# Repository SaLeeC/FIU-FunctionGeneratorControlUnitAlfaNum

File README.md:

# FIU-FunctionGeneratorControlUnitAlfaNum
FIU - Function Generator Control Unit Alphanumeric

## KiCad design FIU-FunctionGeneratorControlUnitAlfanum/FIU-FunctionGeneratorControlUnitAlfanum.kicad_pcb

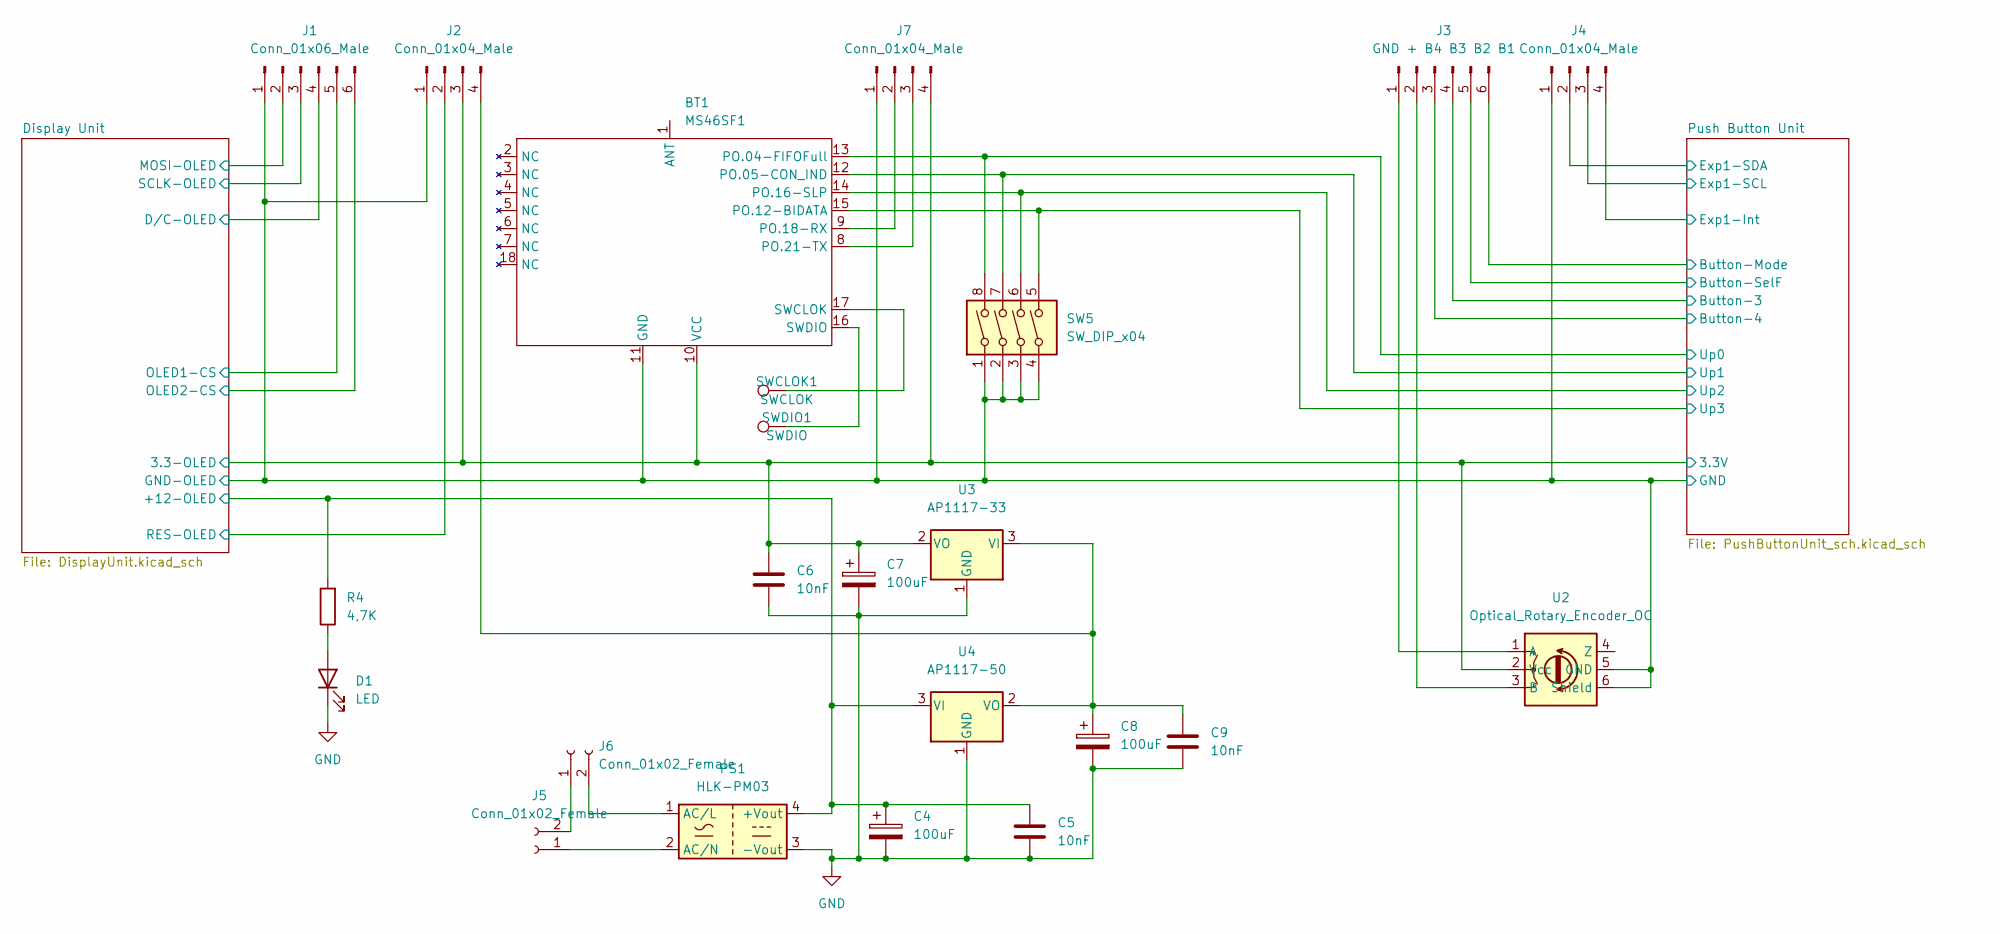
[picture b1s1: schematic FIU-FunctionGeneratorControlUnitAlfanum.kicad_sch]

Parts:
BT1: MS46SF1; MS46SF11
C4, C7, C8: 100uF; CP_Radial_D8.0mm_P5.00mm
C5, C6, C9: 10nF; C_1206_3216Metric
D1: LED; LED_D3.0mm
J1: Conn_01x06_Male; PinHeader_1x06_P2.54mm_Vertical
J2, J4, J7: Conn_01x04_Male; PinHeader_1x04_P2.54mm_Vertical
J3: GND + B4 B3 B2 B1; PinHeader_1x06_P2.54mm_Vertical
J5, J6: Conn_01x02_Female; PinSocket_1x02_P2.54mm_Vertical
PS1: HLK-PM03; CONV_HLK-5M05
R4: 4,7K; R_1206_3216Metric
SW5: SW_DIP_x04; DIP-8_W10.16mm_LongPads
SWCLOK1: SWCLOK; TestPoint_Pad_D1.5mm
SWDIO1: SWDIO; TestPoint_Pad_D1.5mm
U2: Optical_Rotary_Encoder_OC; Rotary Encoder Optical
U3: AP1117-33; SOT-223-3_TabPin2
U4: AP1117-50; SOT-223-3_TabPin2

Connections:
+3V3: BT1.10 (VCC), C6.1, C7.1, J2.3, J7.4, U2.2 (Vcc), U3.2 (VO); also elsewhere on the board
+12V: C4.1, C5.1, PS1.4 (+Vout), R4.2, U4.3 (VI); also elsewhere on the board
/Display Unit/D/C-OLED: J1.4; also elsewhere on the board
/Display Unit/MOSI-OLED: J1.2; also elsewhere on the board
/Display Unit/OLED1-CS: J1.5; also elsewhere on the board
/Display Unit/OLED2-CS: J1.6; also elsewhere on the board
/Display Unit/RES-OLED: J2.2; also elsewhere on the board
/Display Unit/SCLK-OLED: J1.3; also elsewhere on the board
/Push Button Unit/Button-3: J3.4; also elsewhere on the board
/Push Button Unit/Button-4: J3.3; also elsewhere on the board
/Push Button Unit/Button-Mode: J3.6; also elsewhere on the board
/Push Button Unit/Button-SelF: J3.5; also elsewhere on the board
/Push Button Unit/Exp1-Int: J4.4; also elsewhere on the board
/Push Button Unit/Exp1-SCL: J4.3; also elsewhere on the board
/Push Button Unit/Exp1-SDA: J4.2; also elsewhere on the board
/Push Button Unit/Up0: BT1.13 (PO.04-FIFOFull), SW5.8; also elsewhere on the board
/Push Button Unit/Up1: BT1.12 (PO.05-CON_IND), SW5.7; also elsewhere on the board
/Push Button Unit/Up2: BT1.14 (PO.16-SLP), SW5.6; also elsewhere on the board
/Push Button Unit/Up3: BT1.15 (PO.12-BIDATA), SW5.5; also elsewhere on the board
GND: BT1.11 (GND), C4.2, C5.2, C6.2, C7.2, C8.2, C9.2, D1.1 (K), J1.1, J2.1, J4.1, J7.1, PS1.3 (-Vout), SW5.1, SW5.2, SW5.3, SW5.4, U2.5 (GND), U2.6 (Shield), U3.1 (GND), U4.1 (GND); also elsewhere on the board
unnamed: BT1.8 (PO.21-TX), J7.3
unnamed: BT1.9 (PO.18-RX), J7.2
unnamed: BT1.16 (SWDIO), SWDIO1.1
unnamed: BT1.17 (SWCLOK), SWCLOK1.1
unnamed: D1.2 (A), R4.1
unnamed: C8.1, C9.1, J2.4, U3.3 (VI), U4.2 (VO)
unnamed: J3.1, U2.1 (A)
unnamed: J3.2, U2.3 (B)
unnamed 30: J5.1, PS1.2 (AC/N); also elsewhere on the board
unnamed 31: J5.2, J6.1; also elsewhere on the board
unnamed 32: J6.2, PS1.1 (AC/L); also elsewhere on the board

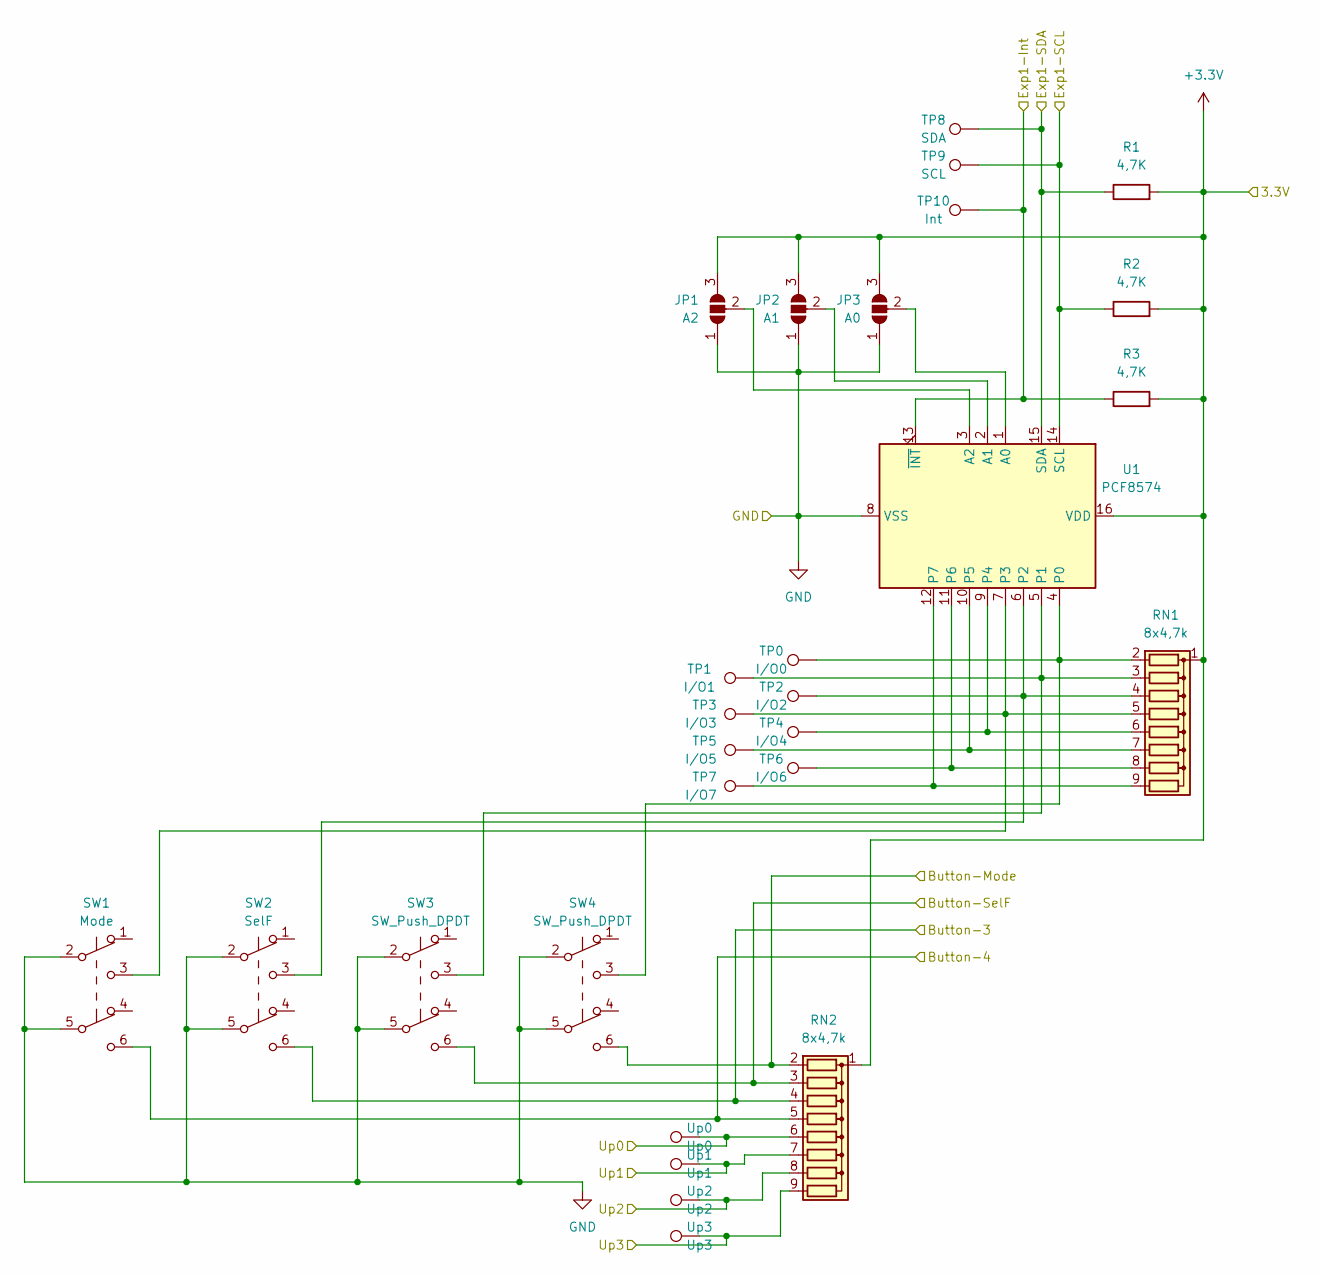
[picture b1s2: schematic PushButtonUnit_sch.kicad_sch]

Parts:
JP1: A2; SolderJumper-3_P1.3mm_Open_RoundedPad1.0x1.5mm
JP2: A1; SolderJumper-3_P1.3mm_Open_RoundedPad1.0x1.5mm
JP3: A0; SolderJumper-3_P1.3mm_Open_RoundedPad1.0x1.5mm
R1, R2, R3: 4,7K; R_1206_3216Metric
RN1, RN2: 8x4,7k; R_Array_SIP9
SW1: Mode; PushDevDouble
SW2: SelF; PushDevDouble
SW3, SW4: SW_Push_DPDT; PushDevDouble
TP0: I/O0; TestPoint_Pad_D1.5mm
TP1: I/O1; TestPoint_Pad_D1.5mm
TP2: I/O2; TestPoint_Pad_D1.5mm
TP3: I/O3; TestPoint_Pad_D1.5mm
TP4: I/O4; TestPoint_Pad_D1.5mm
TP5: I/O5; TestPoint_Pad_D1.5mm
TP6: I/O6; TestPoint_Pad_D1.5mm
TP7: I/O7; TestPoint_Pad_D1.5mm
TP8: SDA; TestPoint_Pad_D1.5mm
TP9: SCL; TestPoint_Pad_D1.5mm
TP10: Int; TestPoint_Pad_D1.5mm
U1: PCF8574; SOIC-16_4.55x10.3mm_P1.27mm
Up0: Up0; TestPoint_Pad_D1.5mm
Up1: Up1; TestPoint_Pad_D1.5mm
Up2: Up2; TestPoint_Pad_D1.5mm
Up3: Up3; TestPoint_Pad_D1.5mm

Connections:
+3V3: JP1.3 (B), JP2.3 (B), JP3.3 (B), R1.2, R2.2, R3.2, RN1.1 (common), RN2.1 (common), U1.16 (VDD); also elsewhere on the board
/Push Button Unit/Button-3: RN2.4 (R3), SW2.6 (C); also elsewhere on the board
/Push Button Unit/Button-4: RN2.5 (R4), SW1.6 (C); also elsewhere on the board
/Push Button Unit/Button-Mode: RN2.2 (R1), SW4.6 (C); also elsewhere on the board
/Push Button Unit/Button-SelF: RN2.3 (R2), SW3.6 (C); also elsewhere on the board
/Push Button Unit/Exp1-Int: R3.1, TP10.1, U1.13 (~INT); also elsewhere on the board
/Push Button Unit/Exp1-SCL: R2.1, TP9.1, U1.14 (SCL); also elsewhere on the board
/Push Button Unit/Exp1-SDA: R1.1, TP8.1, U1.15 (SDA); also elsewhere on the board
/Push Button Unit/Up0: RN2.6 (R5), Up0.1; also elsewhere on the board
/Push Button Unit/Up1: RN2.7 (R6), Up1.1; also elsewhere on the board
/Push Button Unit/Up2: RN2.8 (R7), Up2.1; also elsewhere on the board
/Push Button Unit/Up3: RN2.9 (R8), Up3.1; also elsewhere on the board
GND: JP1.1 (A), JP2.1 (A), JP3.1 (A), SW1.2 (B), SW1.5 (B), SW2.2 (B), SW2.5 (B), SW3.2 (B), SW3.5 (B), SW4.2 (B), SW4.5 (B), U1.8 (VSS); also elsewhere on the board
unnamed: JP1.2 (C), U1.3 (A2)
unnamed: JP2.2 (C), U1.2 (A1)
unnamed: JP3.2 (C), U1.1 (A0)
unnamed: RN1.2 (R1), SW4.3 (C), TP0.1, U1.4 (P0)
unnamed: RN1.3 (R2), SW3.3 (C), TP1.1, U1.5 (P1)
unnamed: RN1.4 (R3), SW2.3 (C), TP2.1, U1.6 (P2)
unnamed: RN1.5 (R4), SW1.3 (C), TP3.1, U1.7 (P3)
unnamed: RN1.6 (R5), TP4.1, U1.9 (P4)
unnamed: RN1.7 (R6), TP5.1, U1.10 (P5)
unnamed: RN1.8 (R7), TP6.1, U1.11 (P6)
unnamed: RN1.9 (R8), TP7.1, U1.12 (P7)

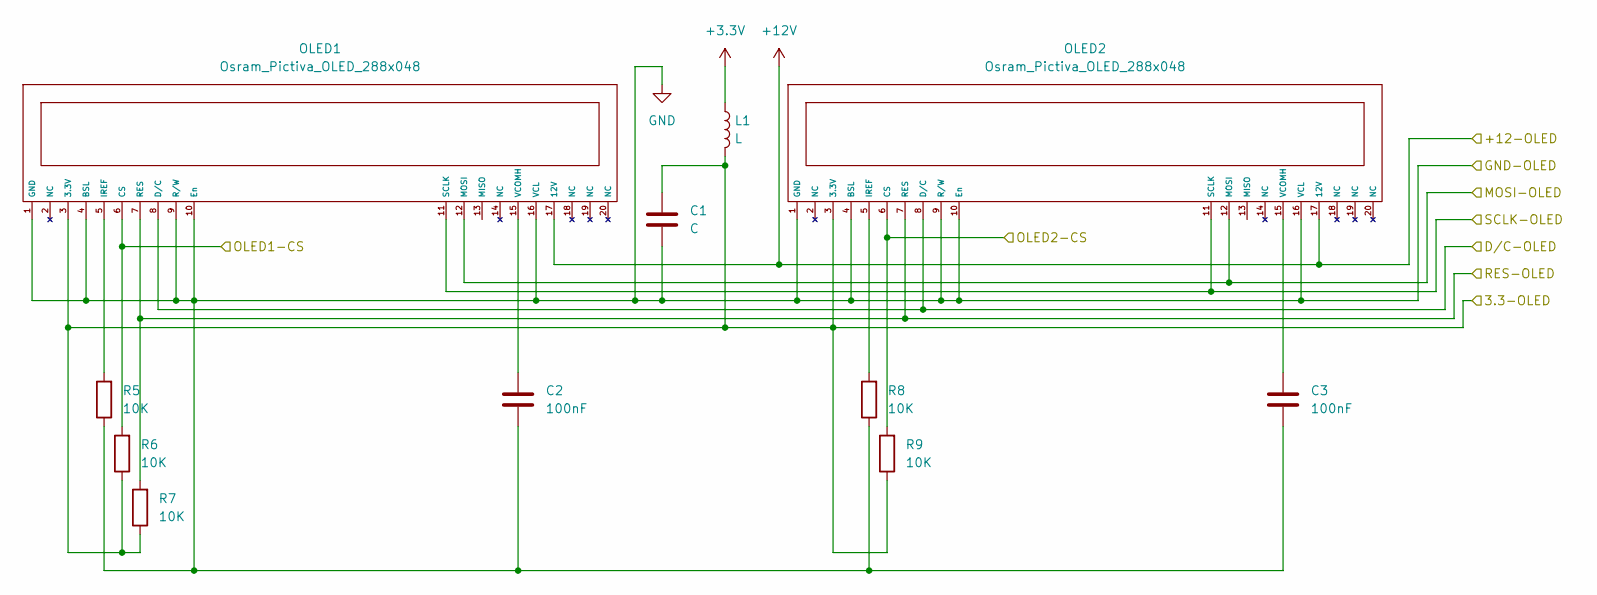
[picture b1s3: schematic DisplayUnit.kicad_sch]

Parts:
C1: C; C_1206_3216Metric
C2, C3: 100nF; C_1206_3216Metric
L1: L; L_1206_3216Metric
OLED1, OLED2: Osram_Pictiva_OLED_288x048; Osram Pictiva 288x048
R5, R6, R7, R8, R9: 10K; R_1206_3216Metric

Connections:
+3V3: C1.1, L1.1, L1.2, OLED1.3 (3.3V), OLED2.3 (3.3V), R6.1, R7.1, R9.1; also elsewhere on the board
+12V: OLED1.17 (12V), OLED2.17 (12V); also elsewhere on the board
/Display Unit/D/C-OLED: OLED1.8 (D/C), OLED2.8 (D/C); also elsewhere on the board
/Display Unit/MOSI-OLED: OLED1.12 (MOSI), OLED2.12 (MOSI); also elsewhere on the board
/Display Unit/OLED1-CS: OLED1.6 (CS), R6.2; also elsewhere on the board
/Display Unit/OLED2-CS: OLED2.6 (CS), R9.2; also elsewhere on the board
/Display Unit/RES-OLED: OLED1.7 (RES), OLED2.7 (RES), R7.2; also elsewhere on the board
/Display Unit/SCLK-OLED: OLED1.11 (SCLK), OLED2.11 (SCLK); also elsewhere on the board
GND: C1.2, C2.2, C3.2, OLED1.1 (GND), OLED1.4 (BSL), OLED1.9 (R/W), OLED1.10 (En), OLED1.16 (VCL), OLED2.1 (GND), OLED2.4 (BSL), OLED2.9 (R/W), OLED2.10 (En), OLED2.16 (VCL), R5.1, R8.1; also elsewhere on the board
unnamed: C2.1, OLED1.15 (VCOMH)
unnamed: C3.1, OLED2.15 (VCOMH)
unnamed: OLED1.5 (IREF), R5.2
unnamed: OLED2.5 (IREF), R8.2

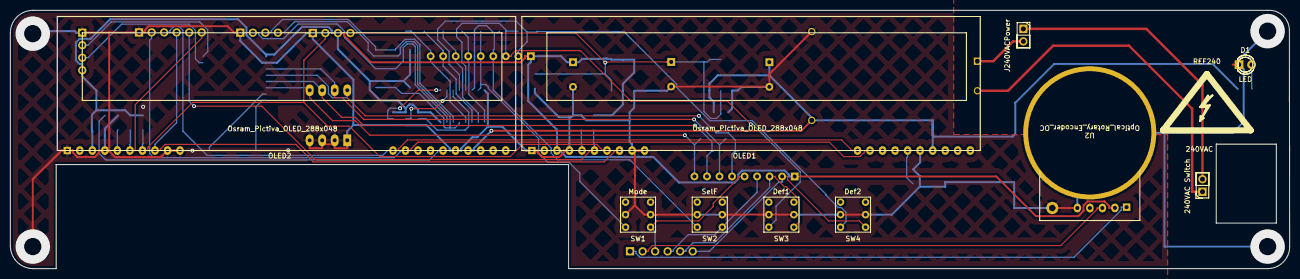
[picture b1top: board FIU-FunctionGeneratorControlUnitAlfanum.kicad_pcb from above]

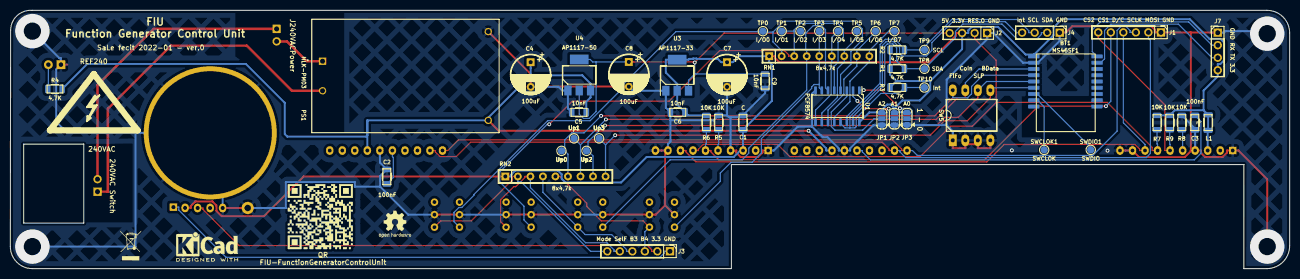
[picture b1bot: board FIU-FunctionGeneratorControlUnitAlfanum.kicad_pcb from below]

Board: 2 copper layers, 259.4 x 52.4 mm, 65 parts (54 on the bottom side), 46 nets.

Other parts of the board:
240VAC Switch: Conn_01x02_Female; PinSocket_1x02_P2.54mm_Vertical
J240VACPower: _; PinSocket_1x02_P2.54mm_Vertical
QR: FIU-FunctionGeneratorControlUnit
REF240, REF240#2: 240VAC; Symbol_Highvoltage_Type2_CopperTop_Small

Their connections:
unnamed 30: 240VAC Switch.1; also elsewhere on the board
unnamed 31: 240VAC Switch.2, J240VACPower.1; also elsewhere on the board
unnamed 32: J240VACPower.2; also elsewhere on the board
